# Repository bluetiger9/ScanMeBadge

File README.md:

# ScanMeBadge

KiCad - KiCad project

InkScape - Inkscape drawing

ScanMeBadge - Arduino example sketch

### Licence

Design files: CC-by-4.0

Example code: MIT

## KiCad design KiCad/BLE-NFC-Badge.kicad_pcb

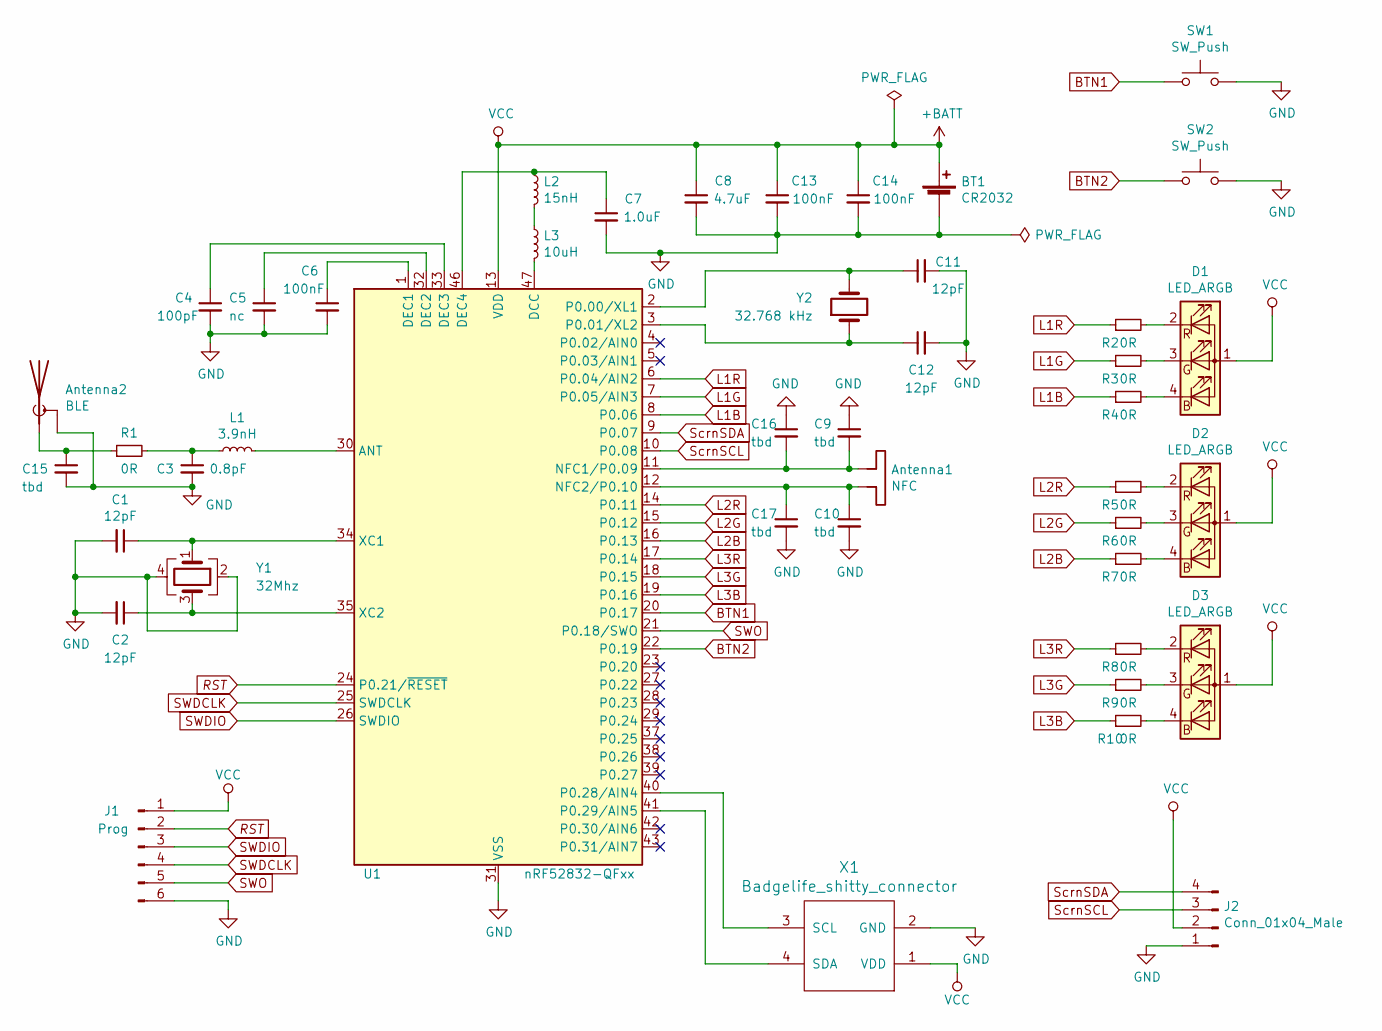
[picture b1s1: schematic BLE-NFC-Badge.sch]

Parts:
Antenna1: NFC
Antenna2: BLE; Texas_SWRA117D_2.4GHz_Right
BT1: CR2032; BatteryHolder_Keystone_1060_1x2032
C1, C2, C11, C12: 12pF; C_0805_2012Metric
C3: 0.8pF; C_0805_2012Metric
C4: 100pF; C_0805_2012Metric
C5: nc; C_0805_2012Metric
C6, C13, C14: 100nF; C_0805_2012Metric
C7: 1.0uF; C_0805_2012Metric
C8: 4.7uF; C_0805_2012Metric
C9, C10, C15, C16, C17: tbd; C_0805_2012Metric
D1, D2, D3: LED_ARGB; LED_Kingbright_AAA3528ESGCT
J1: Prog; PinHeader_1x06_P2.00mm_Pad
J2: Conn_01x04_Male; PinHeader_1x04_P2.54mm_Pad
L1: 3.9nH; L_0805_2012Metric
L2: 15nH; L_0805_2012Metric
L3: 10uH; L_0805_2012Metric
R1, R2, R3, R4, R5, R6, R7, R8, R9, R10: 0R; R_0805_2012Metric
SW1, SW2: SW_Push; SW_SPST_TL3342
U1: nRF52832-QFxx; QFN-48-1EP_6x6mm_P0.4mm_EP4.66x4.66mm
X1: Badgelife_shitty_connector; Badgelife-Shitty-2x2
Y1: 32Mhz; Crystal_SMD_2016-4Pin_2.0x1.6mm
Y2: 32.768 kHz; Crystal_SMD_3215-2Pin_3.2x1.5mm

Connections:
+BATT: BT1.1 (+), C8.1, C13.1, C14.1, D1.1 (A), D2.1 (A), D3.1 (A), J1.1, J2.2, U1.13 (VDD), U1.36 (VDD), U1.48 (VDD), X1.1 (VDD)
BTN1: SW1.1, U1.20 (P0.17)
BTN2: SW2.1, U1.22 (P0.19)
GND: Antenna2.2 (Shield), BT1.2 (-), C1.2, C2.2, C3.2, C4.2, C5.2, C6.2, C7.2, C8.2, C9.1, C10.2, C11.2, C12.2, C13.2, C14.2, C15.2, C16.1, C17.2, J1.6, J2.1, SW1.2, SW2.2, U1.31 (VSS), U1.45 (VSS), U1.49 (VSS), X1.2 (GND), Y1.2, Y1.4
L1B: R4.1, U1.8 (P0.06)
L1G: R3.1, U1.7 (P0.05/AIN3)
L1R: R2.1, U1.6 (P0.04/AIN2)
L2B: R7.1, U1.16 (P0.13)
L2G: R6.1, U1.15 (P0.12)
L2R: R5.1, U1.14 (P0.11)
L3B: R10.1, U1.19 (P0.16)
L3G: R9.1, U1.18 (P0.15)
L3R: R8.1, U1.17 (P0.14)
unnamed: Antenna1.1, C9.2, C16.2, U1.11 (NFC1/P0.09)
unnamed: Antenna1.2, C10.1, C17.1, U1.12 (NFC2/P0.10)
unnamed: Antenna2.1 (A), C15.1, R1.1
unnamed: C1.1, U1.34 (XC1), Y1.1
unnamed: C2.1, U1.35 (XC2), Y1.3
unnamed: C3.1, L1.1, R1.2
unnamed: C4.1, U1.33 (DEC3)
unnamed: C5.1, U1.32 (DEC2)
unnamed: C6.1, U1.1 (DEC1)
unnamed: C7.1, L2.1, U1.46 (DEC4)
unnamed: C11.1, U1.2 (P0.00/XL1), Y2.2
unnamed: C12.1, U1.3 (P0.01/XL2), Y2.1
unnamed: D1.2 (RK), R2.2
unnamed: D1.3 (GK), R3.2
unnamed: D1.4 (BK), R4.2
unnamed: D2.2 (RK), R5.2
unnamed: D2.3 (GK), R6.2
unnamed: D2.4 (BK), R7.2
unnamed: D3.2 (RK), R8.2
unnamed: D3.3 (GK), R9.2
unnamed: D3.4 (BK), R10.2
unnamed: L1.2, U1.30 (ANT)
unnamed: L2.2, L3.1
unnamed: L3.2, U1.47 (DCC)
unnamed: U1.40 (P0.28/AIN4), X1.3 (SCL)
unnamed: U1.41 (P0.29/AIN5), X1.4 (SDA)
RST: J1.2, U1.24 (P0.21/~RESET)
SWDCLK: J1.4, U1.25 (SWDCLK)
SWDIO: J1.3, U1.26 (SWDIO)
SWO: J1.5, U1.21 (P0.18/SWO)
ScrnSCL: J2.3, U1.10 (P0.08)
ScrnSDA: J2.4, U1.9 (P0.07)

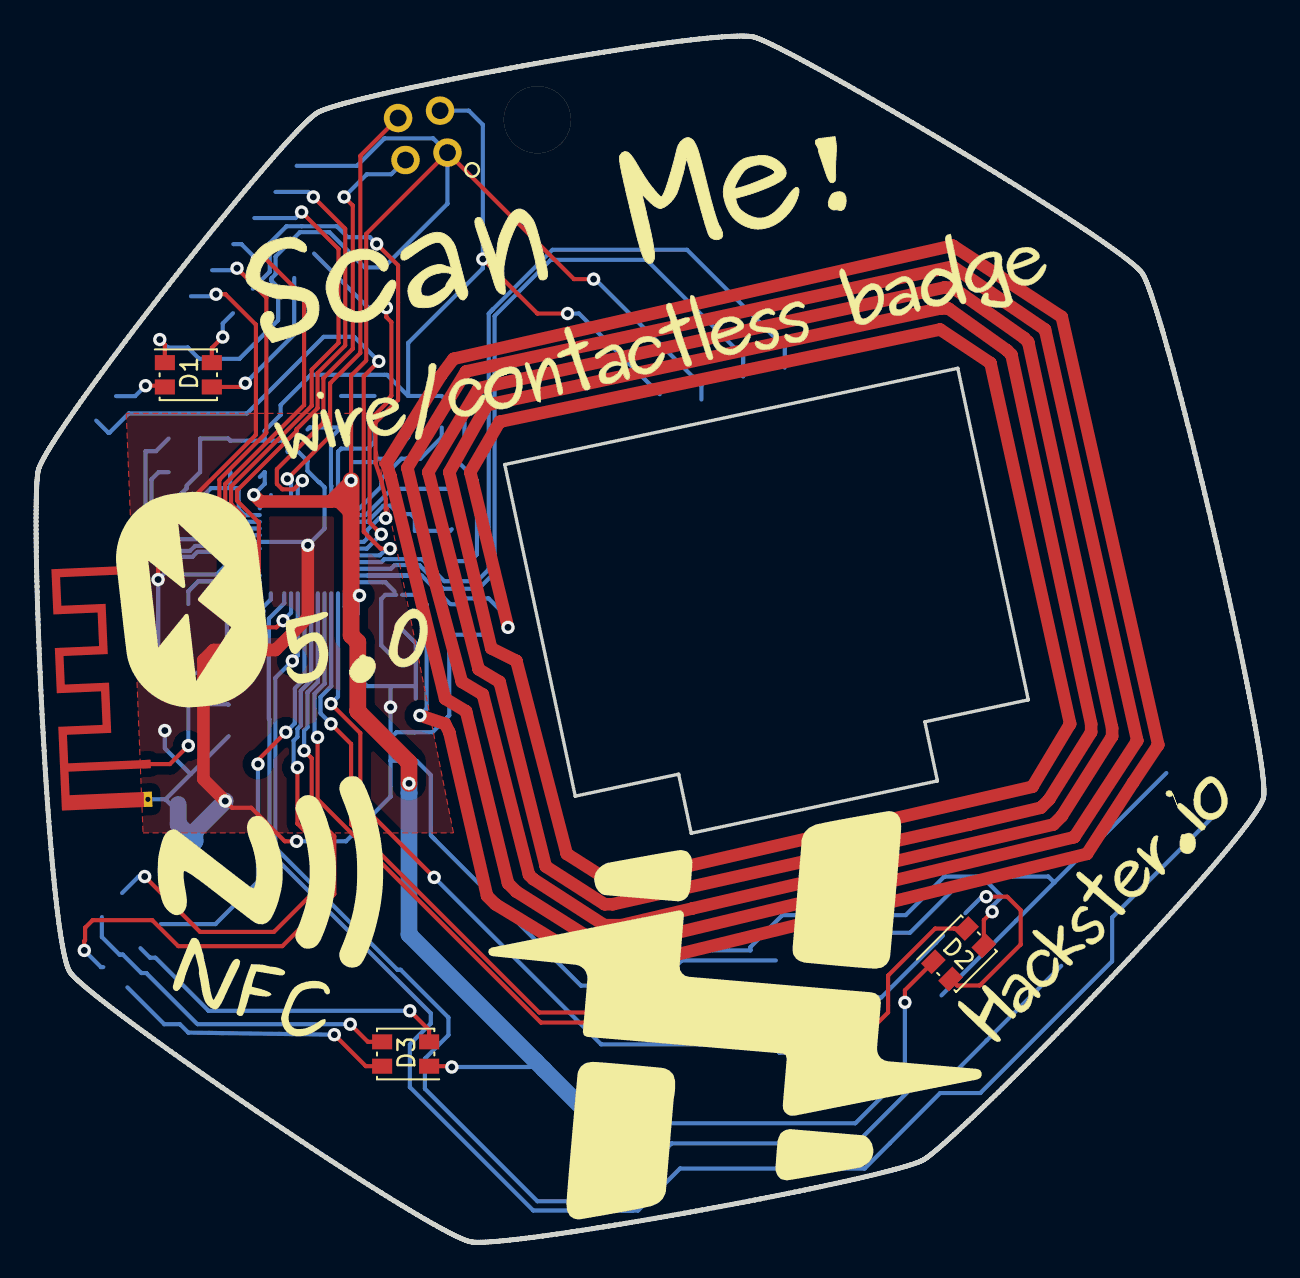
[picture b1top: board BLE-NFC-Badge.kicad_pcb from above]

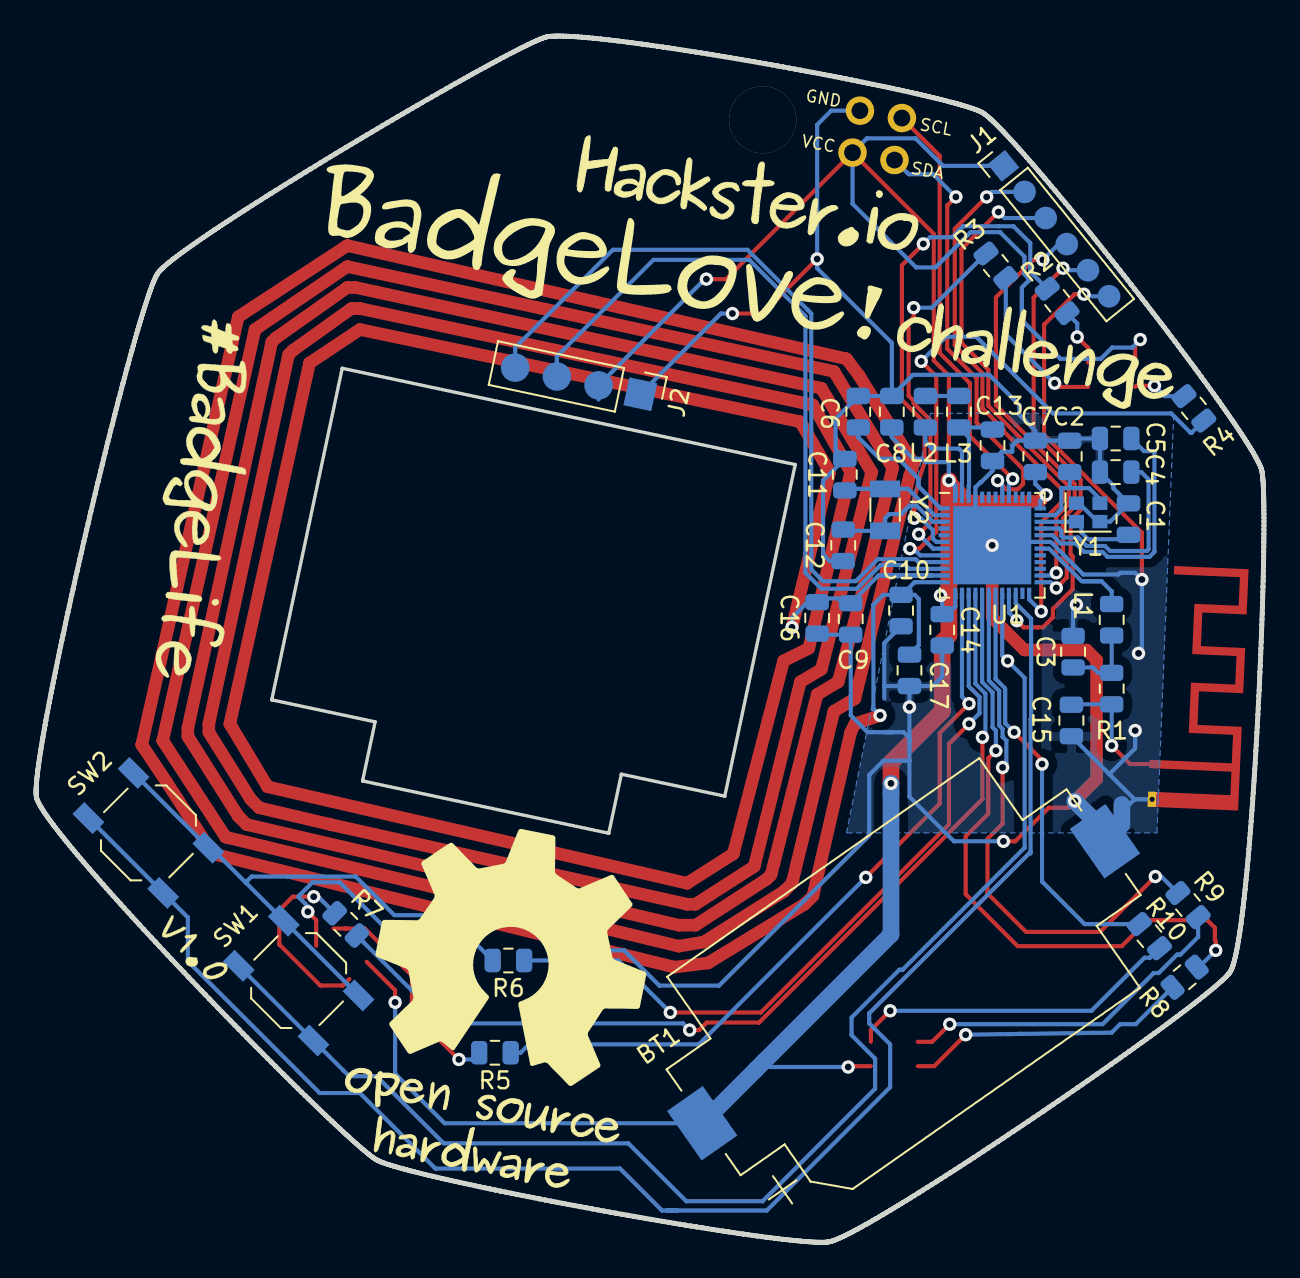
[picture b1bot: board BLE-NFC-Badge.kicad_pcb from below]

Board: 2 copper layers, 73.2 x 71.9 mm, 45 parts (38 on the bottom side), 45 nets.

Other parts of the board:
svg2mod: G***; scan-me-badge-2
svg2mod#2: G***; scan-me-badge
